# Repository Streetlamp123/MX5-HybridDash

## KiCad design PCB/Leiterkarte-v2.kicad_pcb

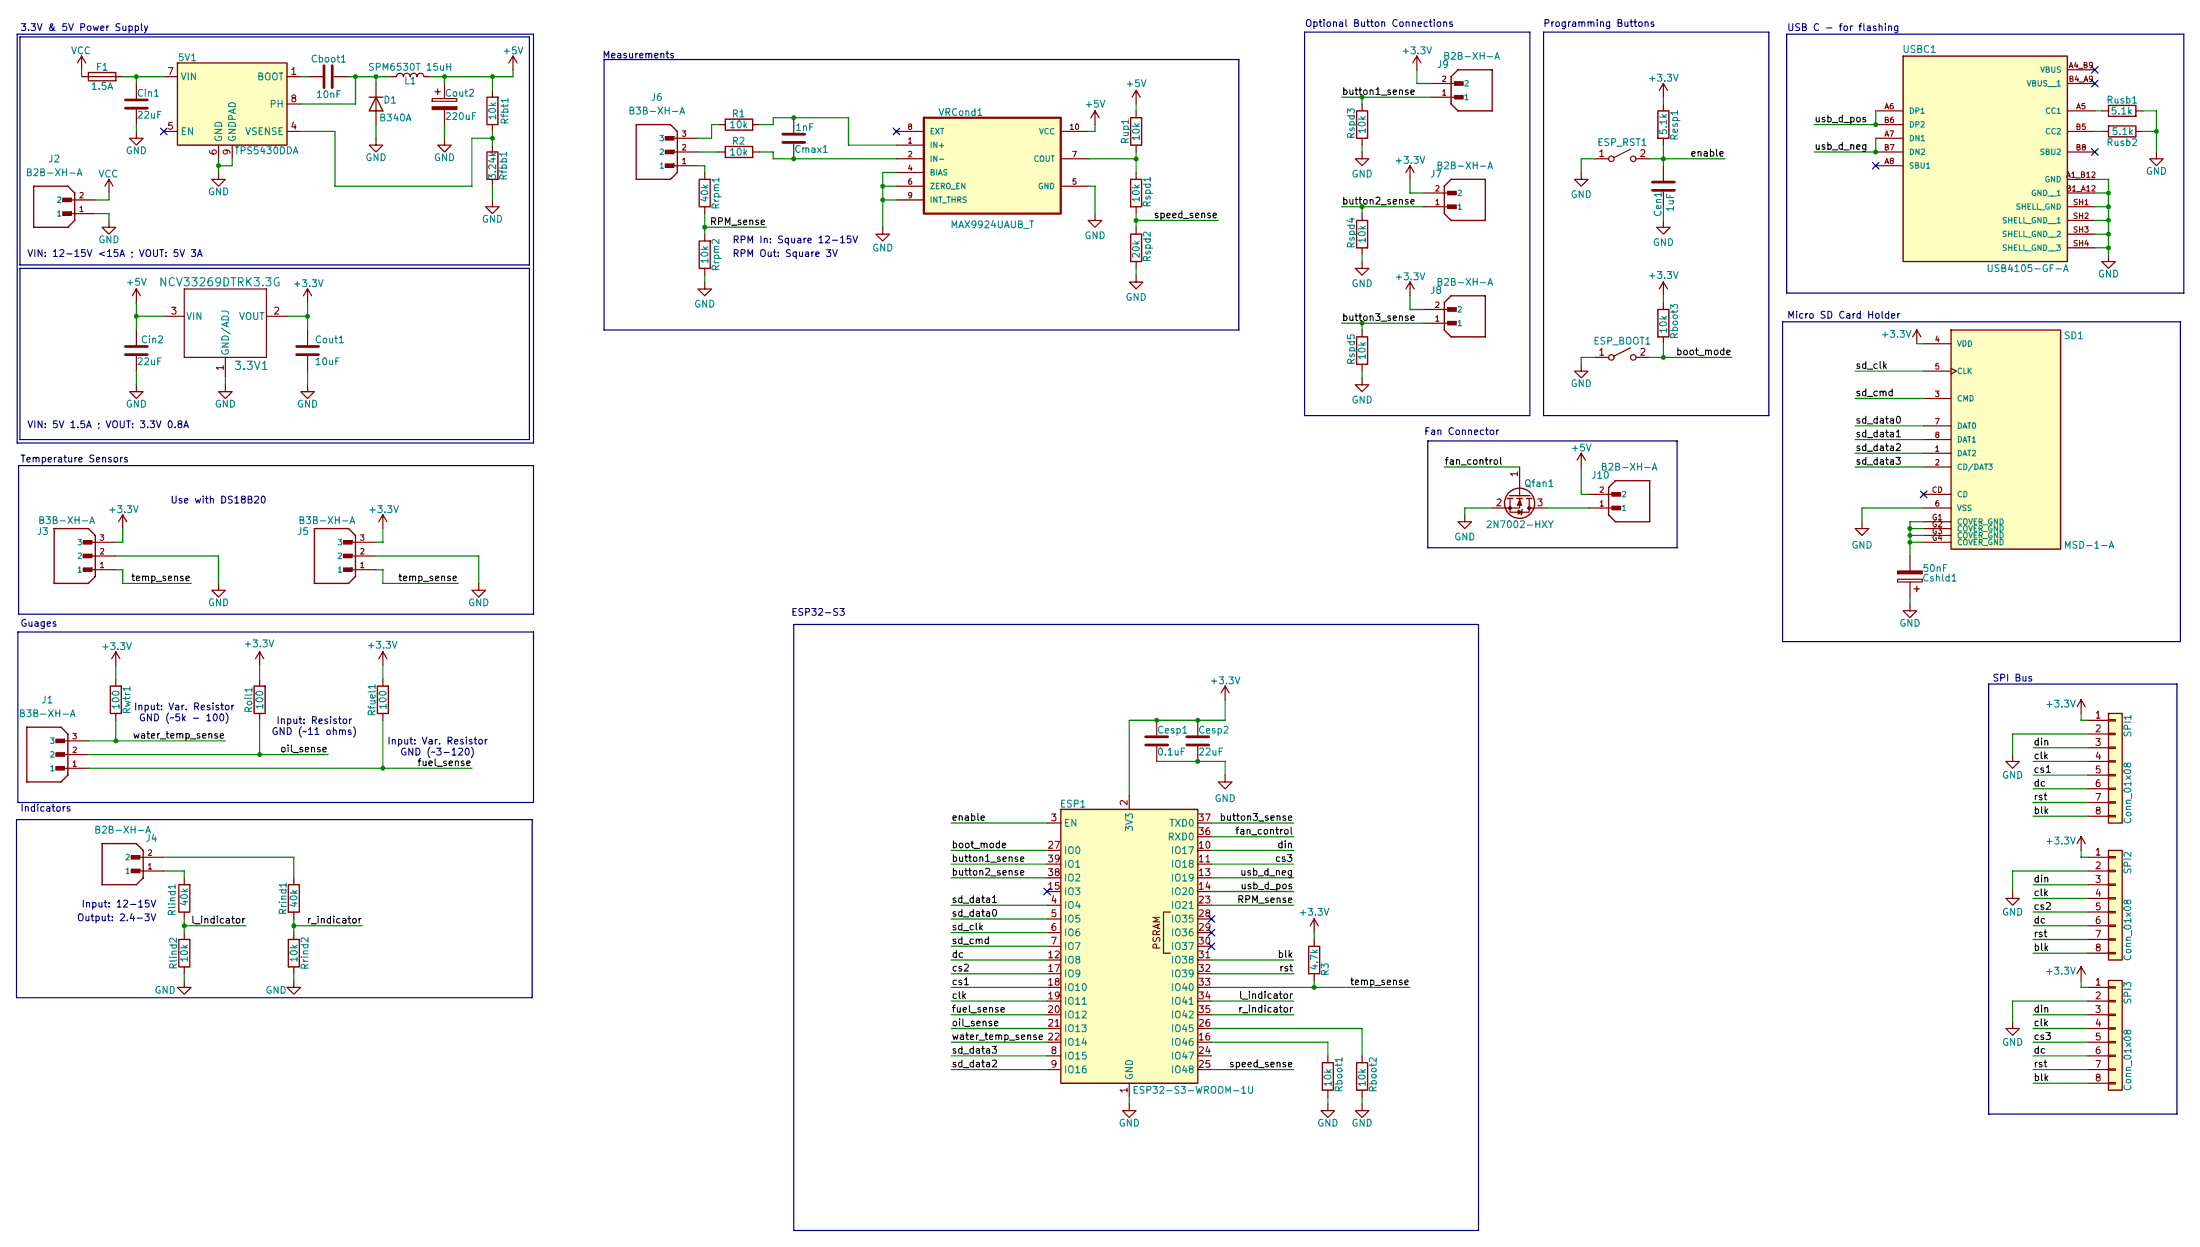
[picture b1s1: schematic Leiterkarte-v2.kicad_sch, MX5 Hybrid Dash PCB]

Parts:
3.3V1: NCV33269DTRK3.3G; DPAK-3_ONS-M
5V1: TPS5430DDA; TI_SO-PowerPAD-8_ThermalVias
Cboot1: 10nF; C_0805_2012Metric
Cen1: 1uF; C_0805_2012Metric
Cesp1: 0.1uF; C_0805_2012Metric
Cesp2: 22uF; C_0805_2012Metric
Cin1, Cin2: 22uF; C_0805_2012Metric
Cmax1: 1nF; C_0805_2012Metric
Cout1: 10uF; C_0805_2012Metric
Cout2: 220uF; CP_Elec_6.3x5.9
Cshld1: 50nF; C_0805_2012Metric
D1: B340A; D_SMA
ESP1: ESP32-S3-WROOM-1U
ESP_BOOT1: SW_SPST; small_button
ESP_RST1: SW_SPST; small_button
F1: 1.5A; Fuse_0603_1608Metric
J1, J3, J5, J6: B3B-XH-A; JST_B3B-XH-A; PARTREV 7/4/21
J2, J4, J7, J8, J9, J10: B2B-XH-A; JST_B2B-XH-A; PARTREV N/A
L1: SPM6530T 15uH; IND_SPM6530T-150M-HZ
Qfan1: 2N7002-HXY; SOT-23
R1, R2: 10k; R_0805_2012Metric
R3: 4.7k; R_0603_1608Metric
Rboot1, Rboot2, Rboot3: 10k; R_0603_1608Metric
Resp1: 5.1k; R_0603_1608Metric
Rfbb1: 3.24k; R_0603_1608Metric
Rfbt1: 10k; R_0603_1608Metric
Rfuel1: 100; R_0603_1608Metric
Rlind1: 40k; R_0603_1608Metric
Rlind2: 10k; R_0603_1608Metric
Roil1: 100; R_0603_1608Metric
Rrind1: 40k; R_0603_1608Metric
Rrind2: 10k; R_0603_1608Metric
Rrpm1: 40k; R_0603_1608Metric
Rrpm2: 10k; R_0603_1608Metric
Rspd1, Rspd3, Rspd4, Rspd5: 10k; R_0603_1608Metric
Rspd2: 20k; R_0603_1608Metric
Rup1: 10k; R_0603_1608Metric
Rusb1, Rusb2: 5.1k; R_0603_1608Metric
Rwtr1: 100; R_0603_1608Metric
SD1: MSD-1-A; CUI_MSD-1-A; PARTREV 1.0
SPI1, SPI2, SPI3: Conn_01x08; JST_SH_BM08B-SRSS-TB_1x08-1MP_P1.00mm_Vertical
USBC1: USB4105-GF-A; GCT_USB4105-GF-A; PARTREV B4
VRCond1: MAX9924UAUB_T; SOP50P490X110-10N

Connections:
+3.3V: 3.3V1.2 (VOUT), Cesp1.1, Cesp2.1, Cout1.1, ESP1.2 (3V3), J3.3, J5.3, J7.2, J8.2, J9.2, R3.1, Rboot3.1, Resp1.1, Rfuel1.2, Roil1.2, Rwtr1.2, SD1.4 (VDD), SPI1.1, SPI2.1, SPI3.1; also elsewhere on the board
+5V: 3.3V1.3 (VIN), Cin2.1, Cout2.1, J10.2, L1.2, Rfbt1.2, Rup1.2, VRCond1.10 (VCC); also elsewhere on the board
/RPM_sense: ESP1.23 (IO21), Rrpm1.1, Rrpm2.2
/blk: ESP1.31 (IO38), SPI1.8, SPI2.8, SPI3.8
/boot_mode: ESP1.27 (IO0), ESP_BOOT1.2 (B), Rboot3.2
/button1_sense: ESP1.39 (IO1), J9.1, Rspd3.1
/button2_sense: ESP1.38 (IO2), J7.1, Rspd4.1
/button3_sense: ESP1.37 (TXD0), J8.1, Rspd5.1
/clk: ESP1.19 (IO11), SPI1.4, SPI2.4, SPI3.4
/cs1: ESP1.18 (IO10), SPI1.5
/cs2: ESP1.17 (IO9), SPI2.5
/cs3: ESP1.11 (IO18), SPI3.5
/dc: ESP1.12 (IO8), SPI1.6, SPI2.6, SPI3.6
/din: ESP1.10 (IO17), SPI1.3, SPI2.3, SPI3.3
/enable: Cen1.2, ESP1.3 (EN), ESP_RST1.2 (B), Resp1.2
/fan_control: ESP1.36 (RXD0), Qfan1.1 (G)
/fuel_sense: ESP1.20 (IO12), J1.1, Rfuel1.1
/l_indicator: ESP1.34 (IO41), Rlind1.1, Rlind2.2
/oil_sense: ESP1.21 (IO13), J1.2, Roil1.1
/r_indicator: ESP1.35 (IO42), Rrind1.2, Rrind2.1
/rst: ESP1.32 (IO39), SPI1.7, SPI2.7, SPI3.7
/sd_clk: ESP1.6 (IO6), SD1.5 (CLK)
/sd_cmd: ESP1.7 (IO7), SD1.3 (CMD)
/sd_data0: ESP1.5 (IO5), SD1.7 (DAT0)
/sd_data1: ESP1.4 (IO4), SD1.8 (DAT1)
/sd_data2: ESP1.9 (IO16), SD1.1 (DAT2)
/sd_data3: ESP1.8 (IO15), SD1.2 (CD/DAT3)
/speed_sense: ESP1.25 (IO48), Rspd1.2, Rspd2.1
/temp_sense: ESP1.33 (IO40), J3.1, J5.1, R3.2
/usb_d_neg: ESP1.13 (IO19), USBC1.A7 (DN1), USBC1.B7 (DN2)
/usb_d_pos: ESP1.14 (IO20), USBC1.A6 (DP1), USBC1.B6 (DP2)
/water_temp_sense: ESP1.22 (IO14), J1.3, Rwtr1.1
GND: 3.3V1.1 (GND/ADJ), 5V1.6 (GND), 5V1.9 (GNDPAD), Cen1.1, Cesp1.2, Cesp2.2, Cin1.2, Cin2.2, Cout1.2, Cout2.2, Cshld1.1, D1.2 (A), ESP1.1 (GND), ESP1.40 (GND), ESP1.41 (GND), ESP_BOOT1.1 (A), ESP_RST1.1 (A), J2.1, J3.2, J5.2, Qfan1.2 (S), Rboot1.2, Rboot2.2, Rfbb1.2, Rlind2.1, Rrind2.2, Rrpm2.1, Rspd2.2, Rspd3.2, Rspd4.2, Rspd5.2, Rusb1.2, Rusb2.1, SD1.6 (VSS), SPI1.2, SPI2.2, SPI3.2, USBC1.A1_B12 (GND), USBC1.B1_A12 (GND__1), USBC1.SH1 (SHELL_GND), USBC1.SH2 (SHELL_GND__1), USBC1.SH3 (SHELL_GND__2), USBC1.SH4 (SHELL_GND__3), VRCond1.4 (BIAS), VRCond1.5 (GND), VRCond1.6 (ZERO_EN), VRCond1.9 (INT_THRS); also elsewhere on the board
unnamed: 5V1.1 (BOOT), Cboot1.2
unnamed: 5V1.8 (PH), Cboot1.1, D1.1 (K), L1.1
unnamed: 5V1.7 (VIN), Cin1.1, F1.2
unnamed: 5V1.4 (VSENSE), Rfbb1.1, Rfbt1.1
unnamed: Cshld1.2, SD1.G1 (COVER_GND), SD1.G2 (COVER_GND), SD1.G3 (COVER_GND), SD1.G4 (COVER_GND)
unnamed: ESP1.26 (IO45), Rboot2.1
unnamed: ESP1.16 (IO46), Rboot1.1
unnamed: J4.1, Rlind1.2
unnamed: J4.2, Rrind1.1
unnamed: J6.1, Rrpm1.2
unnamed: J6.2, R2.1
unnamed: J6.3, R1.1
unnamed: J10.1, Qfan1.3 (D)
unnamed: Rusb1.1, USBC1.A5 (CC1)
unnamed: Rusb2.2, USBC1.B5 (CC2)
unnamed: Rspd1.1, Rup1.1, VRCond1.7 (COUT)
unnamed: Cmax1.2, R1.2, VRCond1.1 (IN+)
unnamed: Cmax1.1, R2.2, VRCond1.2 (IN-)
VCC: F1.1, J2.2

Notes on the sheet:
Fan Connector
Guages
Optional Button Connections
Measurements
Input: Resistor GND (~11 ohms)
ESP32-S3
Input: Var. Resistor GND (~3-120)
VIN: 5V 1.5A ; VOUT: 3.3V 0.8A
Programming Buttons
Micro SD Card Holder
VIN: 12-15V <15A ; VOUT: 5V 3A
3.3V & 5V Power Supply
RPM Out: Square 3V
RPM In: Square 12-15V
Output: 2.4-3V
Temperature Sensors
Use with DS18B20
Input: Var. Resistor GND (~5k - 100)
Indicators
Input: 12-15V
USB C - for flashing
SPI Bus

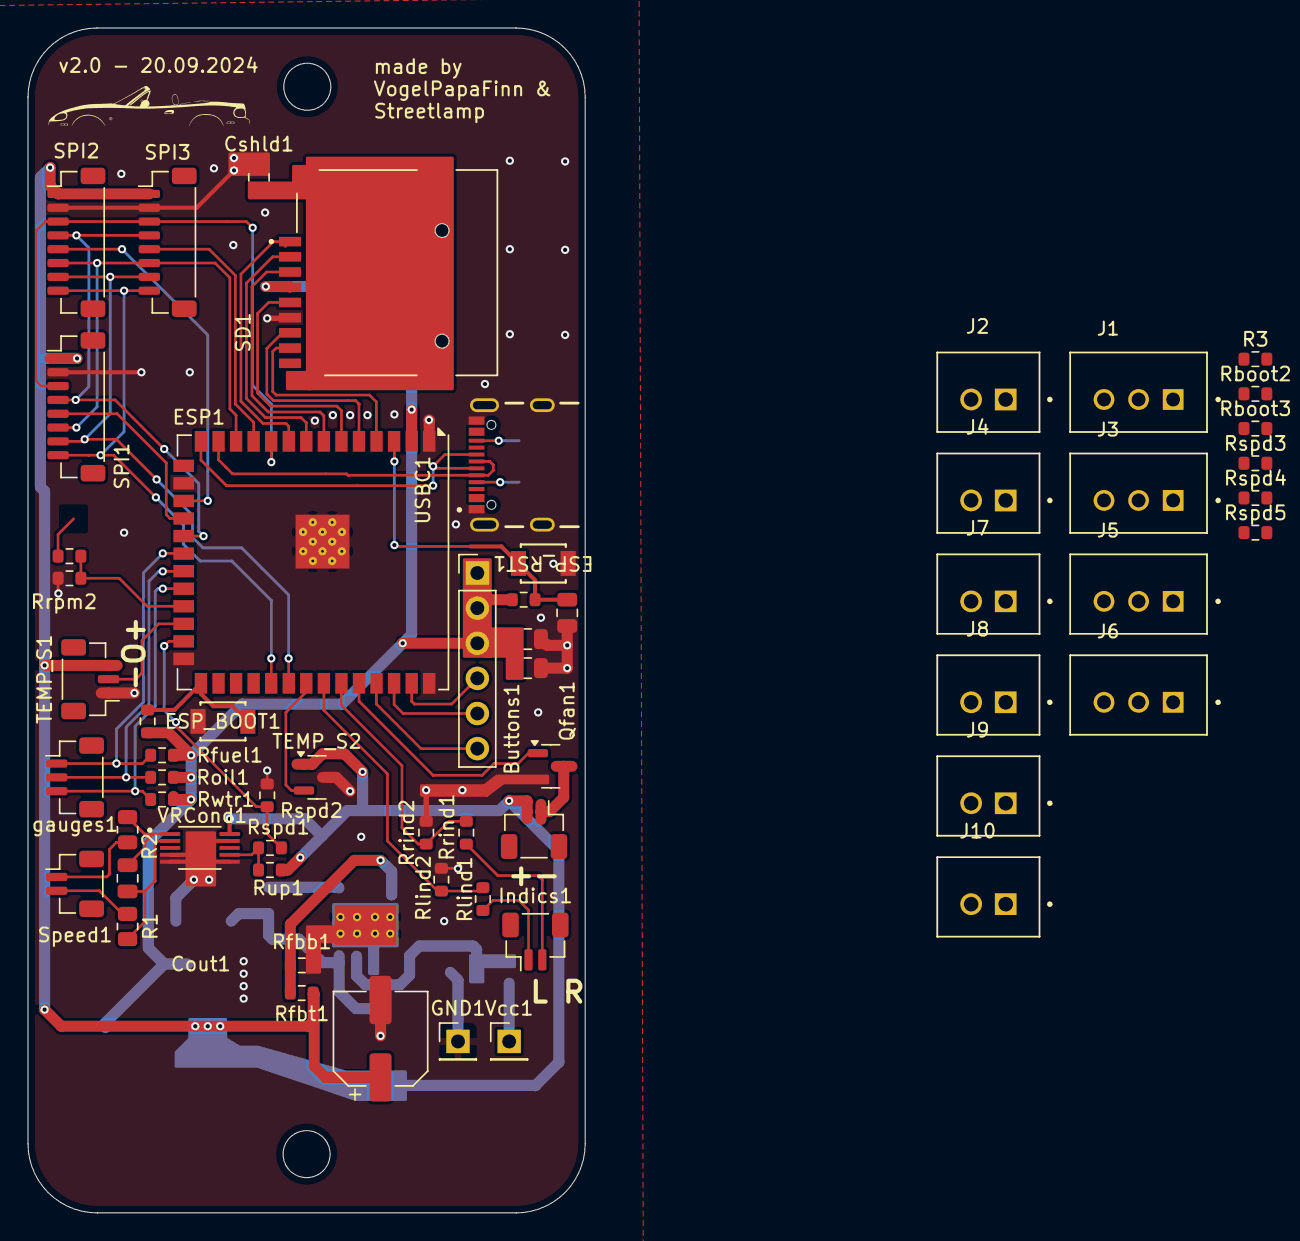
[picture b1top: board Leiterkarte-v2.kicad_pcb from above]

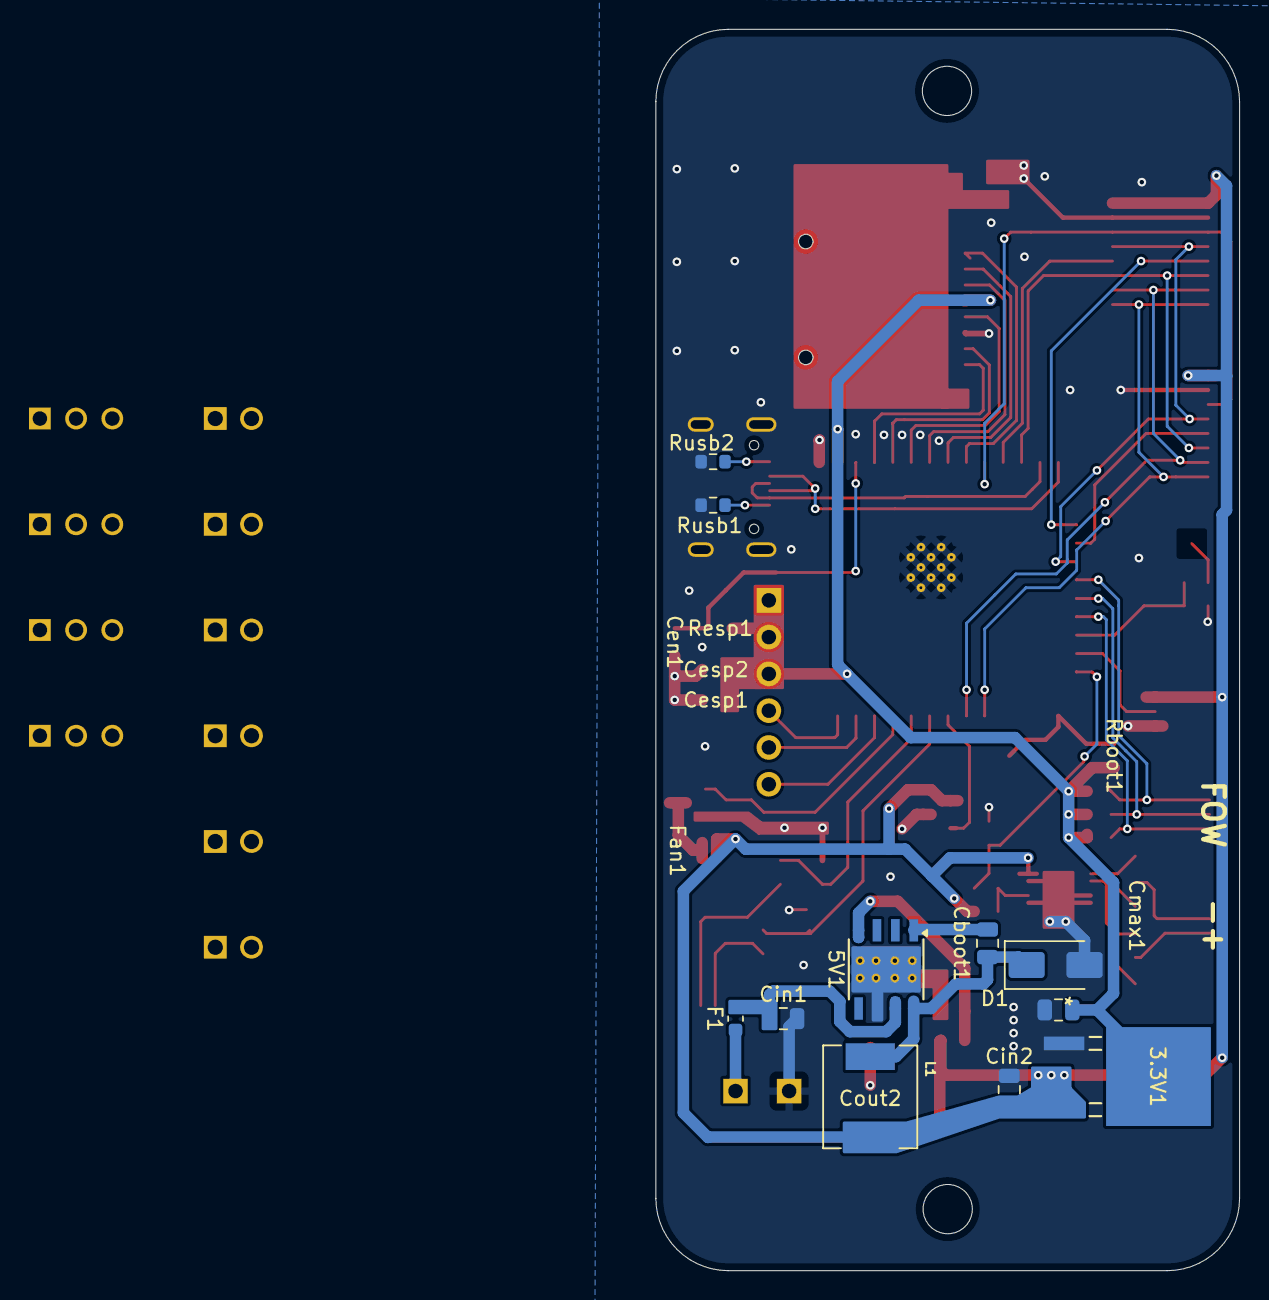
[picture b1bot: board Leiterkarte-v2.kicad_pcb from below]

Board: 4 copper layers, 40.3 x 85.7 mm, 70 parts (11 on the bottom side), 52 nets.

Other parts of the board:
Buttons1: Conn_01x06_Pin; PinHeader_1x06_P2.54mm_Vertical
Fan1: Conn_01x02_Pin; JST_SH_BM02B-SRSS-TB_1x02-1MP_P1.00mm_Vertical
GND1: Conn_01x01_Pin; PinHeader_1x01_P2.54mm_Vertical
Indics1: Conn_01x02_Pin; JST_SH_BM02B-SRSS-TB_1x02-1MP_P1.00mm_Vertical
Speed1: Conn_01x02_Pin; JST_SH_BM02B-SRSS-TB_1x02-1MP_P1.00mm_Vertical
TEMP_S1: Conn_01x03_Pin; JST_SH_BM03B-SRSS-TB_1x03-1MP_P1.00mm_Vertical
TEMP_S2: MCP9700Ax-ETT; SOT-23
Vcc1: Conn_01x01_Pin; PinHeader_1x01_P2.54mm_Vertical
gauges1: Conn_01x03_Pin; JST_SH_BM03B-SRSS-TB_1x03-1MP_P1.00mm_Vertical

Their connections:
+3.3V: Buttons1.1, Buttons1.2, Buttons1.3; also elsewhere on the board
+5V: Fan1.2, TEMP_S1.3, TEMP_S2.1 (V_{DD}); also elsewhere on the board
GND: GND1.1, TEMP_S1.1, TEMP_S2.3 (GND); also elsewhere on the board

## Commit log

2024-09-29 reorganization
